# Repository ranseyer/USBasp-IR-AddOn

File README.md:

USBasp-IR-AddOn
===============

IR-Reciver  Extension for USBASP

ir_control, 1.0.0 (20.05.2012) control the "USB IR Remote Receiver"
 (www.mikrocontroller.net/articles/USB_IR_Remote_Receiver).

ir_control [-h] | [-V] | [[[-d] | [-p[1|0]] | [-rCOUNT] | [-s] | [-t]] [-i]]

  -h              print this help and exit
  -V              print version and exit

  -d              delete the PowerOn IR code.
                  The next received code becomes the new PowerOn code
  -p [1|0]        set PowerOn (ON=1/OFF=0)
  -r COUNT        set repeat count (default=5)
  -s              status of: PowerOn (ON=1/OFF=0)
  -i              ignore device name. (just checks the vendor:device ID)
                  needs one of the other options.

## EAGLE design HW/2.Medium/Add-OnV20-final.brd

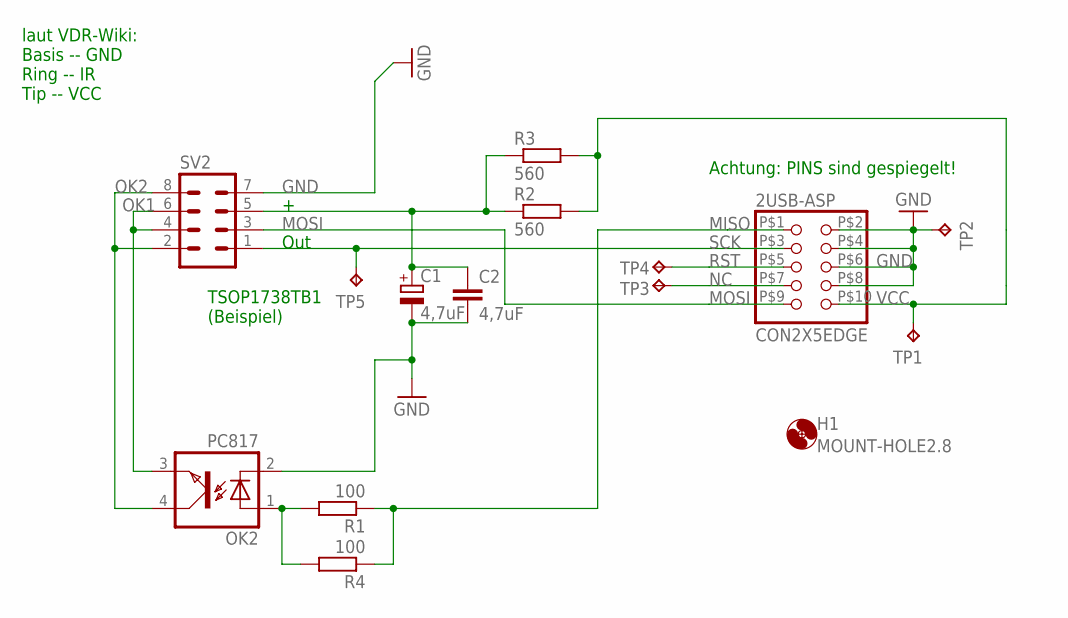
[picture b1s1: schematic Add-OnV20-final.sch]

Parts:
2USB-ASP: CON2X5EDGE
C1: 4,7uF; E1,8-4
C2: 4,7uF; C1206K
H1: MOUNT-HOLE2.8; 2,8
OK2: PC817; DIL04
R1: 100; 0204/7
R2: 560; 0204/7
R3: 560; R0805W
R4: 100; R0805W
SV2: MA04-2
TP1, TP2, TP3, TP4, TP5: TPB1,27; B1,27

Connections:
GND: 2USB-ASP.P$2 (2), 2USB-ASP.P$4 (4), 2USB-ASP.P$6 (6), 2USB-ASP.P$8 (8), C1.-, C2.2, OK2.2 (C), SV2.7, TP2.TP
MISO: 2USB-ASP.P$1 (1), R1.1, R4.1
MOSI: 2USB-ASP.P$9 (9), SV2.3
unnamed: C1.+, C2.1, R2.1, R3.1, SV2.5
unnamed: OK2.1 (A), R1.2, R4.2
NC: 2USB-ASP.P$7 (7), TP3.TP
OK1: OK2.3 (EMIT), SV2.4, SV2.6
OK2: OK2.4 (COL), SV2.2, SV2.8
RST: 2USB-ASP.P$5 (5), TP4.TP
SCK: 2USB-ASP.P$3 (3), SV2.1, TP5.TP
VCC: 2USB-ASP.P$10 (10), R2.2, R3.2, TP1.TP

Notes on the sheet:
Achtung: PINS sind gespiegelt!
Out
laut VDR-Wiki: Basis -- GND Ring -- IR Tip -- VCC
TSOP1738TB1 (Beispiel)

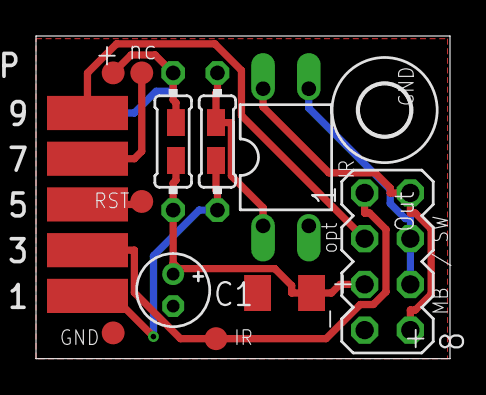
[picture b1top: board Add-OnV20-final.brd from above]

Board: 2 copper layers, 23.0 x 17.9 mm, 15 parts (0 on the bottom side), 11 nets.

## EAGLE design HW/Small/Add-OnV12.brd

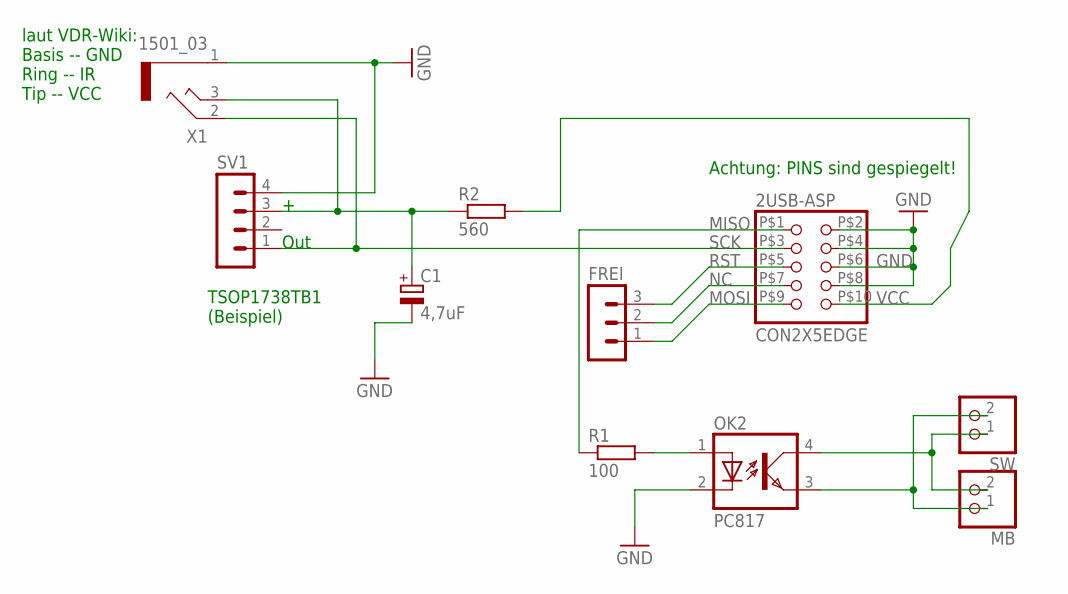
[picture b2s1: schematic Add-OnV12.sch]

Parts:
2USB-ASP: CON2X5EDGE
C1: 4,7uF; E1,8-4
FREI: MA03-1
MB: PINHD-1X2; 1X02
OK2: PC817; DIL04
R1: 100; 0204V
R2: 560; 0204V
SV1: MA04-1
SW: PINHD-1X2; 1X02
X1: 1501_03

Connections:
GND: 2USB-ASP.P$2 (2), 2USB-ASP.P$4 (4), 2USB-ASP.P$6 (6), 2USB-ASP.P$8 (8), C1.-, OK2.2 (C), SV1.4, X1.1
MISO: 2USB-ASP.P$1 (1), R1.1
MOSI: 2USB-ASP.P$9 (9), FREI.1
unnamed: C1.+, R2.1, SV1.3, X1.3
unnamed: OK2.1 (A), R1.2
unnamed: MB.2, OK2.4 (COL), SW.1
unnamed: MB.1, OK2.3 (EMIT), SW.2
NC: 2USB-ASP.P$7 (7), FREI.2
RST: 2USB-ASP.P$5 (5), FREI.3
SCK: 2USB-ASP.P$3 (3), SV1.1, X1.2
VCC: 2USB-ASP.P$10 (10), R2.2

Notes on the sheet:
Achtung: PINS sind gespiegelt!
Out
laut VDR-Wiki: Basis -- GND Ring -- IR Tip -- VCC
TSOP1738TB1 (Beispiel)

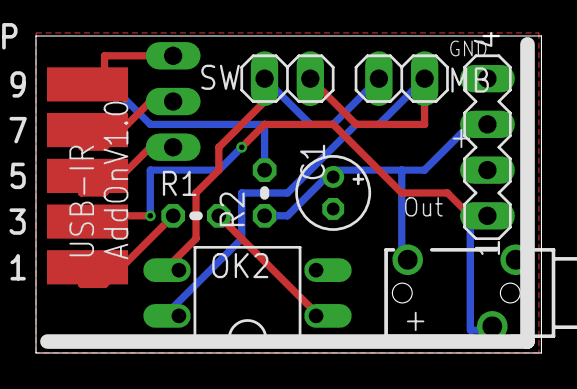
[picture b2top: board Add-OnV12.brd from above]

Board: 2 copper layers, 28.1 x 17.6 mm, 10 parts (1 on the bottom side), 11 nets.

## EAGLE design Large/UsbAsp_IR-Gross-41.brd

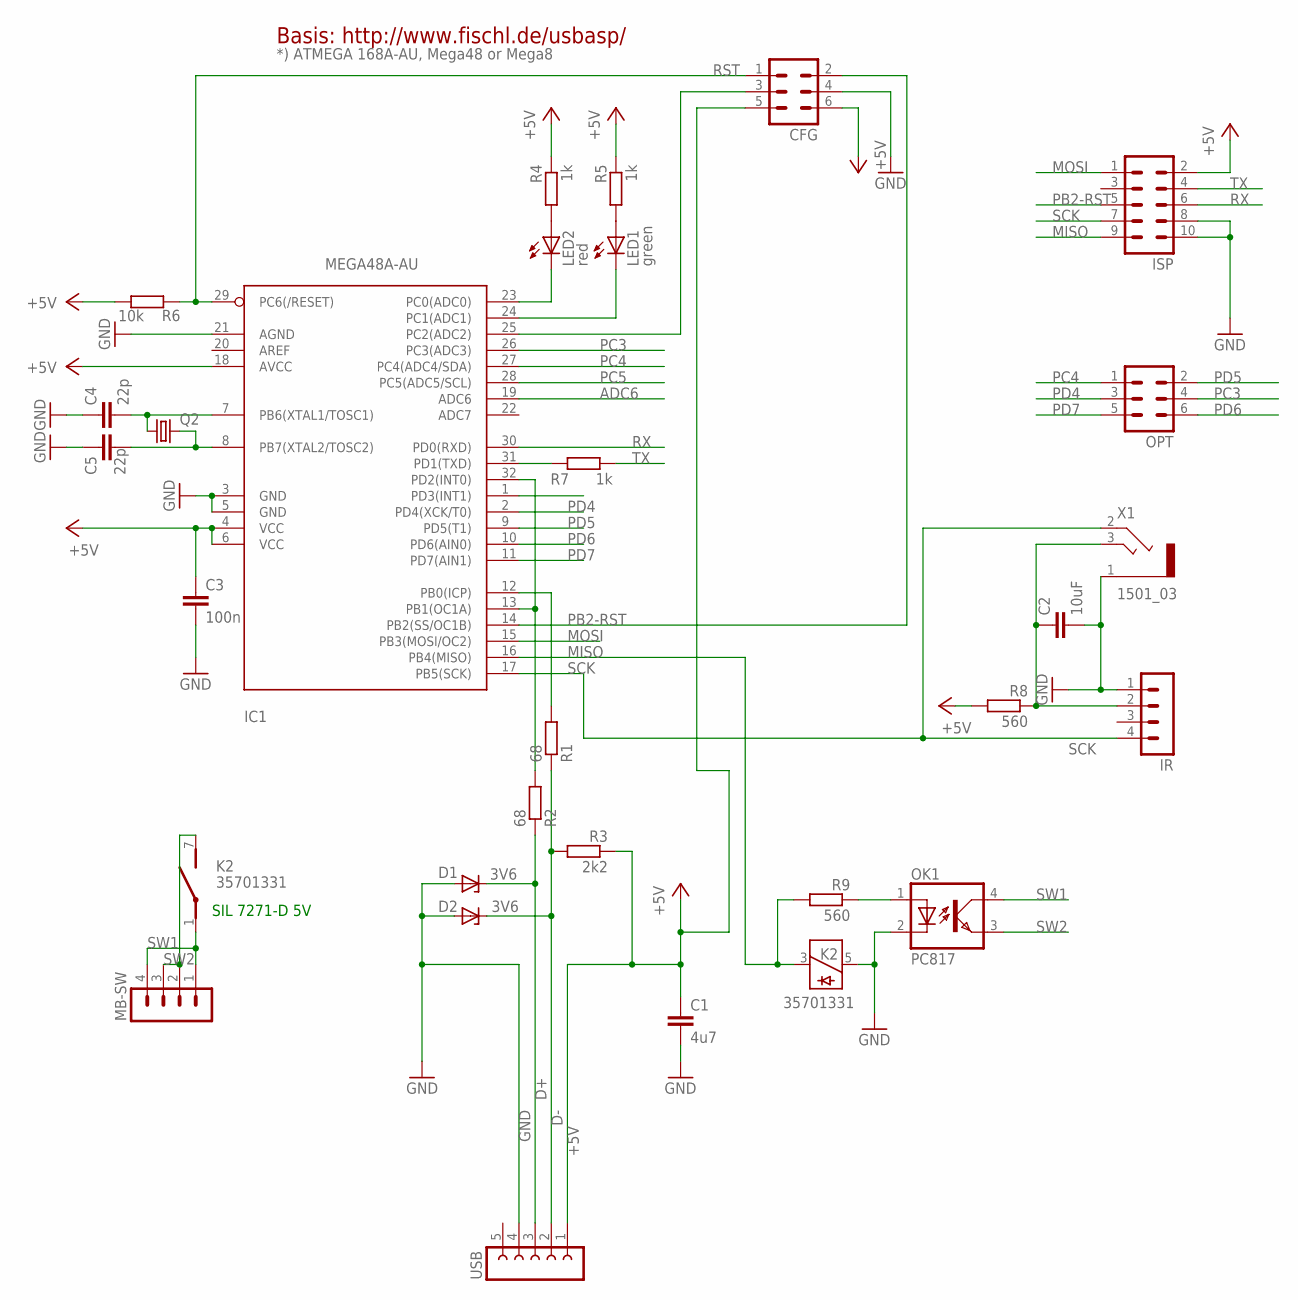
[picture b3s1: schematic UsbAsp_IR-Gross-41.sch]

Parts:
C1: 4u7; C0805
C2: 10uF; C1210
C3: 100n; C0805
C4, C5: 22p; C0805
CFG: MA03-2
D1, D2: 3V6; SOD80C
IC1: MEGA48A-AU; TQFP32-08
IR: MA04-1
ISP: MA05-2
K2: 35701331; REED
LED1: green; CHIPLED_1206
LED2: red; CHIPLED_1206
MB-SW: MA04-1
OK1: PC817; DIL04
OPT: MA03-2
Q2: CRYSTALHC49UP; HC49UP
R1, R2: 68; M0805
R3: 2k2; M0805
R4, R5, R7: 1k; M0805
R6: 10k; M0805
R8, R9: 560; M0805
USB: FE05W
X1: 1501_03

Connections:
+5V: C1.1, C3.1, CFG.5, CFG.6, IC1.4 (VCC), IC1.6 (VCC), IC1.18 (AVCC), ISP.2, R3.1, R4.1, R5.1, R6.1, R8.2, USB.1
ADC6: IC1.19 (ADC6)
D+: D1.C, R2.1, USB.3
D-: D2.C, R1.1, R3.2, USB.2
GND: C1.2, C2.2, C3.2, C4.1, C5.1, CFG.4, D1.A, D2.A, IC1.3 (GND), IC1.5 (GND), IC1.21 (AGND), IR.1, ISP.8, ISP.10, K2.5, OK1.2 (C), USB.4, X1.1
MISO: IC1.16 (PB4(MISO)), ISP.9, K2.3, R9.2
MOSI: IC1.15 (PB3(MOSI/OC2)), ISP.1
unnamed: OK1.1 (A), R9.1
unnamed: CFG.3, IC1.25 (PC2(ADC2))
unnamed: C2.1, IR.2, R8.1, X1.3
unnamed: IC1.31 (PD1(TXD)), R7.2
unnamed: IC1.13 (PB1(OC1A)), IC1.32 (PD2(INT0)), R2.2
unnamed: LED2.A, R4.2
unnamed: IC1.23 (PC0(ADC0)), LED2.C
unnamed: IC1.24 (PC1(ADC1)), LED1.C
unnamed: IC1.12 (PB0(ICP)), R1.2
unnamed: C4.2, IC1.7 (PB6(XTAL1/TOSC1)), Q2.1
unnamed: C5.2, IC1.8 (PB7(XTAL2/TOSC2)), Q2.2
unnamed: LED1.A, R5.2
PB2-RST: CFG.2, IC1.14 (PB2(SS/OC1B)), ISP.5
PC3: IC1.26 (PC3(ADC3)), OPT.4
PC4: IC1.27 (PC4(ADC4/SDA)), OPT.1
PC5: IC1.28 (PC5(ADC5/SCL))
PD4: IC1.2 (PD4(XCK/T0)), OPT.3
PD5: IC1.9 (PD5(T1)), OPT.2
PD6: IC1.10 (PD6(AIN0)), OPT.6
PD7: IC1.11 (PD7(AIN1)), OPT.5
RST: CFG.1, IC1.29 (PC6(/RESET)), R6.2
RX: IC1.30 (PD0(RXD)), ISP.6
SCK: IC1.17 (PB5(SCK)), IR.4, ISP.7, X1.2
SW1: K2.1, MB-SW.1, MB-SW.4, OK1.4 (COL)
SW2: K2.7 (S), MB-SW.2, MB-SW.3, OK1.3 (EMIT)
TX: ISP.4, R7.1

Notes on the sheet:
Basis: http://www.fischl.de/usbasp/
*) ATMEGA 168A-AU, Mega48 or Mega8
SIL 7271-D 5V

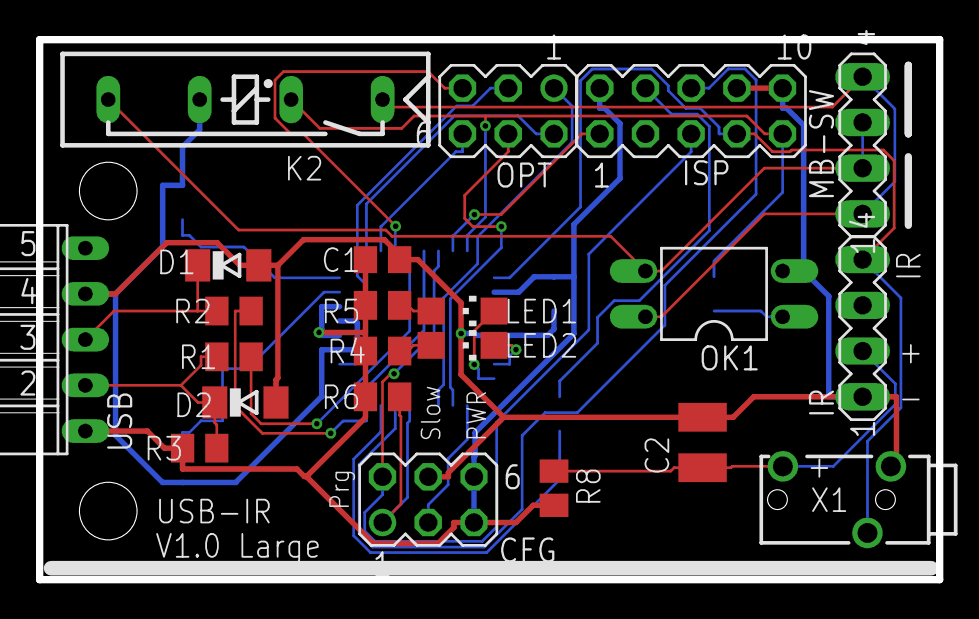
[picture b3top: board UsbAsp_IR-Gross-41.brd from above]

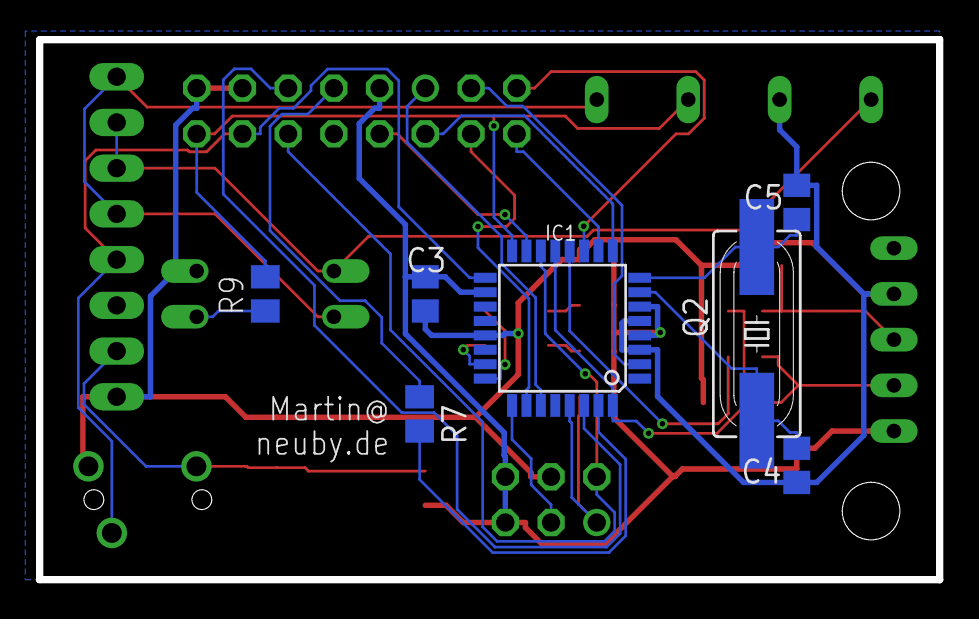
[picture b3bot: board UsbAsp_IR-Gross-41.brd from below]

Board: 2 copper layers, 50.0 x 30.0 mm, 29 parts (7 on the bottom side), 31 nets.

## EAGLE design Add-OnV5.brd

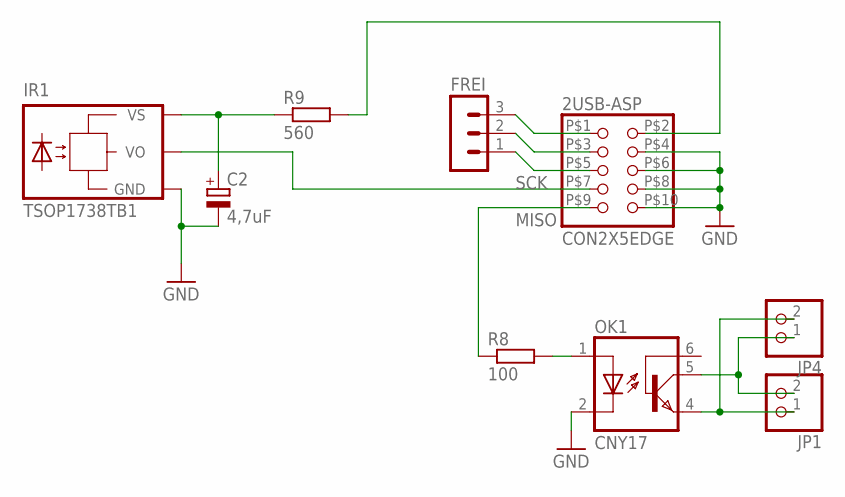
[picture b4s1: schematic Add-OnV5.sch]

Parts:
2USB-ASP: CON2X5EDGE
C2: 4,7uF; E1,8-4
FREI: MA03-1
IR1: TSOP1738TB1; TSOP17_TB1
JP1, JP4: PINHD-1X2; 1X02
OK1: CNY17; DIL06
R8: 100; 0204/7
R9: 560; 0204/7

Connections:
GND: 2USB-ASP.P$4 (4), 2USB-ASP.P$6 (6), 2USB-ASP.P$8 (8), 2USB-ASP.P$10 (10), C2.-, IR1.GND, OK1.2 (C)
MISO: 2USB-ASP.P$9 (9), R8.1
unnamed: C2.+, IR1.VS, R9.1
unnamed: OK1.1 (A), R8.2
unnamed: JP1.2, JP4.1, OK1.5 (COL)
unnamed: JP1.1, JP4.2, OK1.4 (EMI)
unnamed: 2USB-ASP.P$2 (2), R9.2
unnamed: 2USB-ASP.P$5 (5), FREI.1
unnamed: 2USB-ASP.P$3 (3), FREI.2
unnamed: 2USB-ASP.P$1 (1), FREI.3
SCK: 2USB-ASP.P$7 (7), IR1.VO

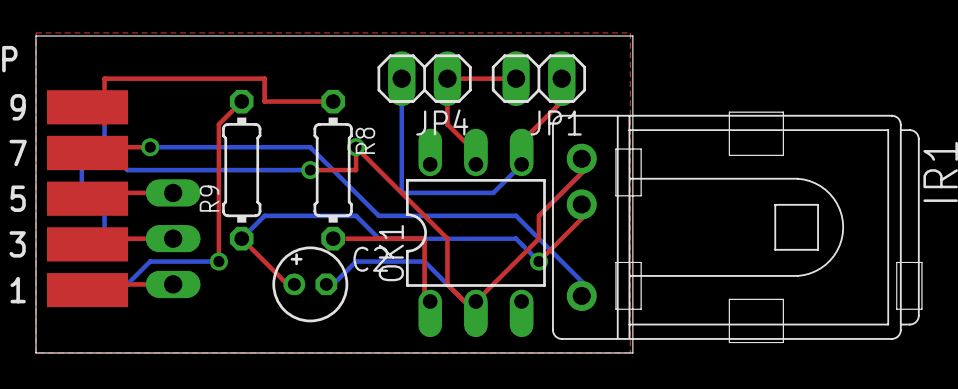
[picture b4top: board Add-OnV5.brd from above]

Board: 2 copper layers, 49.2 x 17.6 mm, 9 parts (1 on the bottom side), 11 nets.

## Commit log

2013-03-21 1st Upload
2013-03-22 Optimized
2013-03-24 Mirrored Plug
    for using the the cable of USB-ASP...
2013-03-24 Mini-Version
    Use without Cable
2013-03-24 Mini as JPG...
2013-03-29 Large
    +Cleanup
2013-03-29 Large Images
2013-04-07 Partlists
2013-04-12 Final Layout
2013-05-05 Missing BRD
2013-11-17 Doku
2013-11-17 cleanup
2013-11-17 Reorg+Software
2013-11-20 Mini V1.1
2013-12-19 Fix PortD
    PORTD &=~(1<<PD2); /* deactivate pull-up on int0 line */
2013-12-23 Update Doku
2014-01-03 fix ir_control 1st try
2014-01-03 IR-Control: added "repeat"
    Thanks to Wirbel und Bleifuss2
2014-01-04 Fix Repeat Rate
    Thanks again to Wirbel + Bleifuss2
2014-01-25 Repeat rate fix by woggle
    From here
    http://www.vdr-portal.de/board16-video-disk-recorder/board4-vdr-installation/p1183244-gel%C3%B6st-samsung-fernbedienung-mit-usb-ir-receiver-einrichten/#post1183244
2014-03-16 m168
    Binarys
2014-03-31 New Layout V2
2014-03-31 Mega168-Large
    with more Remotes...
2014-05-13 Optimized V2
2014-11-01 Slotblech (Draft)
2014-11-01 FiX Repeat Rate by hitman47
    Source:
    http://www.easy-vdr.de/forum/index.php?topic=16032.msg153985#msg153985
2014-12-04 Mega8 Fix
2014-12-15 Doku +/- changed
